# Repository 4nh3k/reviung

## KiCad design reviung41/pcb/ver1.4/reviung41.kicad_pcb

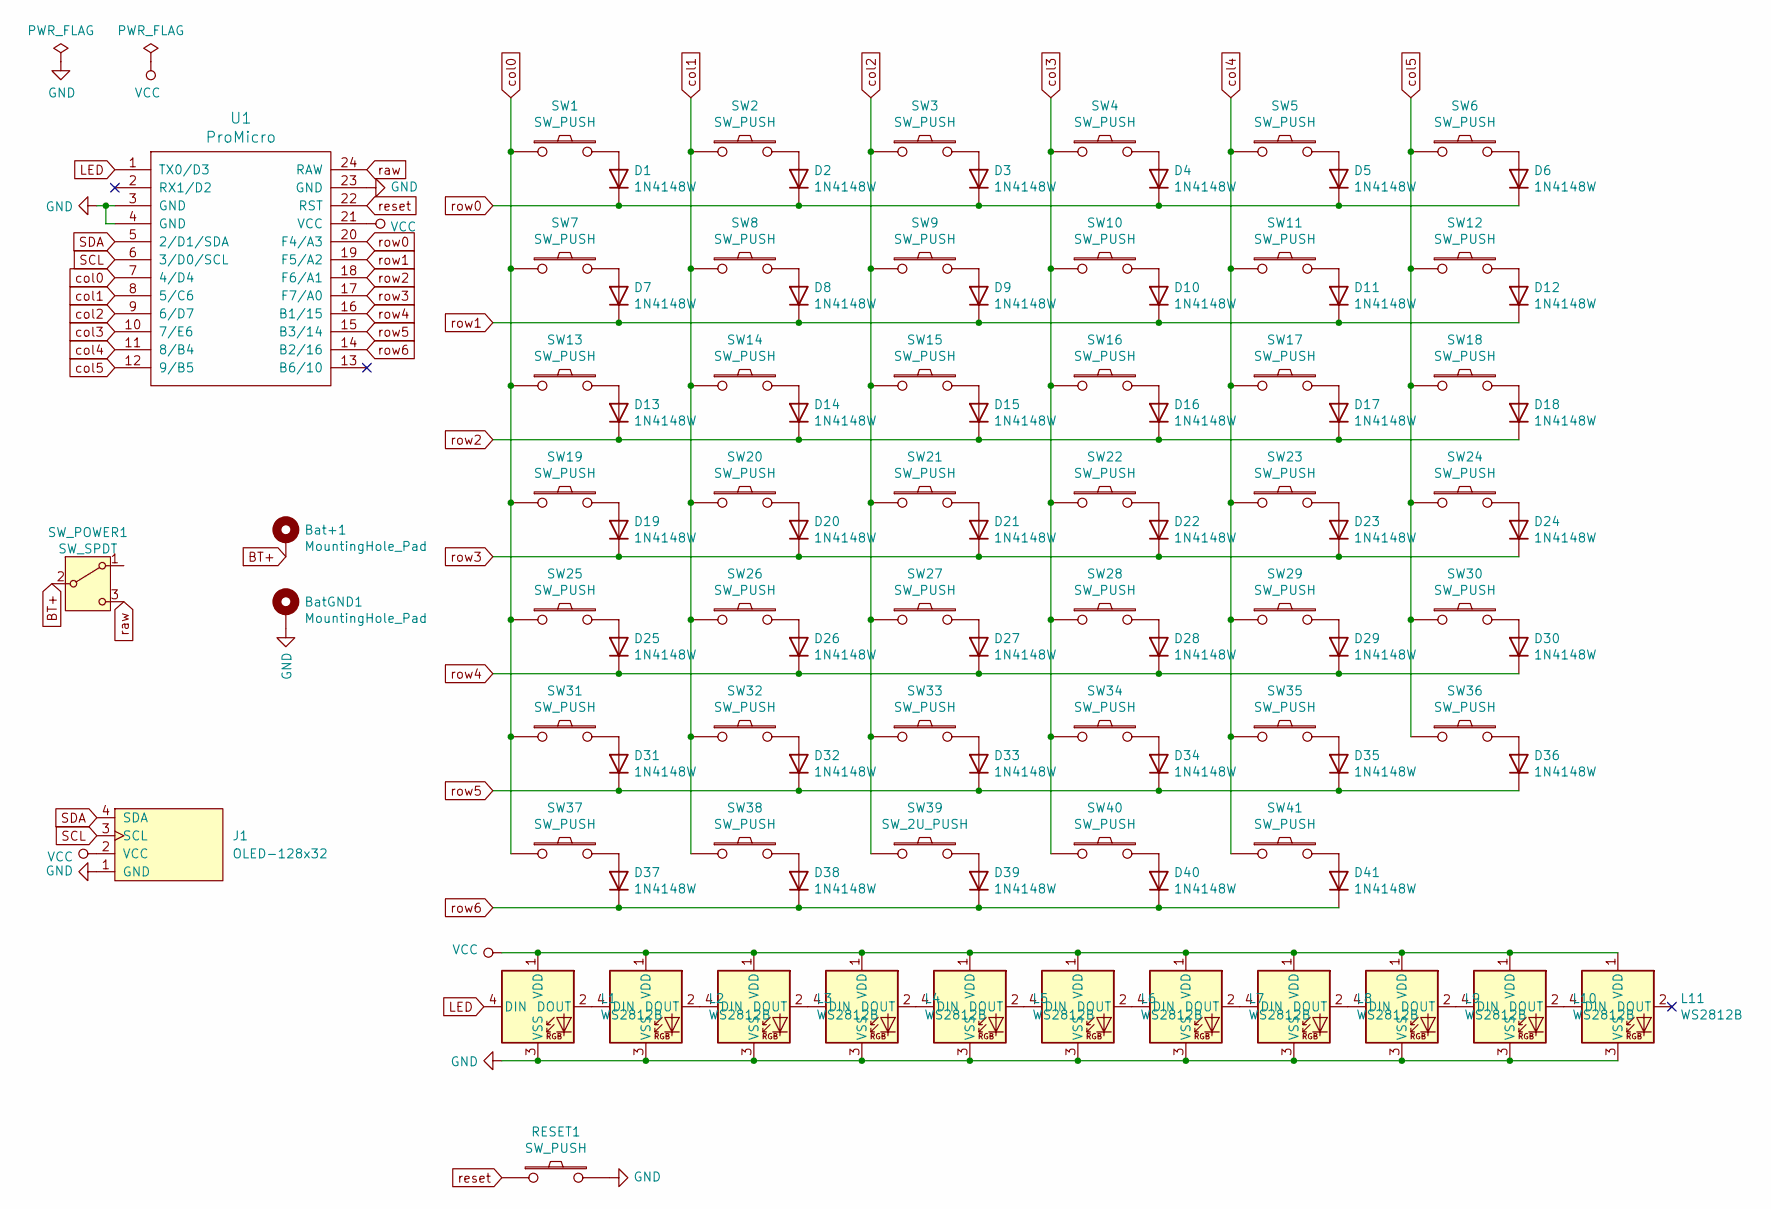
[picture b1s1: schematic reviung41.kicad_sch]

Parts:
Bat+1: MountingHole_Pad; batteryhole
BatGND1: MountingHole_Pad; batteryhole
D1, D2, D3, D4, D5, D6, D7, D8, D9, D10, D11, D12, D13, D14, D15, D16, D17, D18, D19, D20, D21, D22, D23, D24, D25, D26, D27, D28, D29, D30, D31, D32, D33, D34, D35, D36, D37, D38, D39, D40, D41: 1N4148W; D3_SMD_1side
J1: OLED-128x32; SSD1306-0.91-OLED-4pin-128x32
L1, L2, L3, L4, L5, L6, L7, L8, L9, L10, L11: WS2812B; LED_WS2812B_PLCC4_5.0x5.0mm_P3.2mm
RESET1: SW_PUSH; ResetSW_1side
SW1, SW2, SW3, SW4, SW5, SW6, SW7, SW8, SW9, SW10, SW11, SW12, SW13, SW14, SW15, SW16, SW17, SW18, SW19, SW20, SW21, SW22, SW23, SW24, SW25, SW26, SW27, SW28, SW29, SW30, SW31, SW32, SW33, SW34, SW35, SW36, SW37, SW38, SW40, SW41: SW_PUSH; MXOnly-1U-Hotswap
SW39: SW_2U_PUSH; MXOnly-2U-Hotswap-ReversedStabilizers
SW_POWER1: SW_SPDT; SW_SPDT_PCM12
U1: ProMicro

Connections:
BT+: Bat+1.1, SW_POWER1.2 (B)
GND: BatGND1.1, J1.1 (GND), L1.3 (VSS), L2.3 (VSS), L3.3 (VSS), L4.3 (VSS), L5.3 (VSS), L6.3 (VSS), L7.3 (VSS), L8.3 (VSS), L9.3 (VSS), L10.3 (VSS), L11.3 (VSS), RESET1.2, U1.3 (GND), U1.4 (GND), U1.23 (GND)
LED: L1.4 (DIN), U1.1 (TX0/D3)
unnamed: D1.2 (A), SW1.2
unnamed: D2.2 (A), SW2.2
unnamed: D3.2 (A), SW3.2
unnamed: D4.2 (A), SW4.2
unnamed: D5.2 (A), SW5.2
unnamed: D6.2 (A), SW6.2
unnamed: D7.2 (A), SW7.2
unnamed: D8.2 (A), SW8.2
unnamed: D9.2 (A), SW9.2
unnamed: D10.2 (A), SW10.2
unnamed: D11.2 (A), SW11.2
unnamed: D12.2 (A), SW12.2
unnamed: D13.2 (A), SW13.2
unnamed: D14.2 (A), SW14.2
unnamed: D15.2 (A), SW15.2
unnamed: D16.2 (A), SW16.2
unnamed: D17.2 (A), SW17.2
unnamed: D18.2 (A), SW18.2
unnamed: D19.2 (A), SW19.2
unnamed: D20.2 (A), SW20.2
unnamed: D21.2 (A), SW21.2
unnamed: D22.2 (A), SW22.2
unnamed: D23.2 (A), SW23.2
unnamed: D24.2 (A), SW24.2
unnamed: D25.2 (A), SW25.2
unnamed: D26.2 (A), SW26.2
unnamed: D27.2 (A), SW27.2
unnamed: D28.2 (A), SW28.2
unnamed: D29.2 (A), SW29.2
unnamed: D30.2 (A), SW30.2
unnamed: D31.2 (A), SW31.2
unnamed: D32.2 (A), SW32.2
unnamed: D33.2 (A), SW33.2
unnamed: D34.2 (A), SW34.2
unnamed: D35.2 (A), SW35.2
unnamed: D36.2 (A), SW36.2
unnamed: D37.2 (A), SW37.2
unnamed: D38.2 (A), SW38.2
unnamed: D39.2 (A), SW39.2
unnamed: D40.2 (A), SW40.2
unnamed: D41.2 (A), SW41.2
unnamed: L1.2 (DOUT), L2.4 (DIN)
unnamed: L2.2 (DOUT), L3.4 (DIN)
unnamed: L3.2 (DOUT), L4.4 (DIN)
unnamed: L4.2 (DOUT), L5.4 (DIN)
unnamed: L5.2 (DOUT), L6.4 (DIN)
unnamed: L6.2 (DOUT), L7.4 (DIN)
unnamed: L7.2 (DOUT), L8.4 (DIN)
unnamed: L8.2 (DOUT), L9.4 (DIN)
unnamed: L9.2 (DOUT), L10.4 (DIN)
unnamed: L10.2 (DOUT), L11.4 (DIN)
SCL: J1.3 (SCL), U1.6 (3/D0/SCL)
SDA: J1.4 (SDA), U1.5 (2/D1/SDA)
VCC: J1.2 (VCC), L1.1 (VDD), L2.1 (VDD), L3.1 (VDD), L4.1 (VDD), L5.1 (VDD), L6.1 (VDD), L7.1 (VDD), L8.1 (VDD), L9.1 (VDD), L10.1 (VDD), L11.1 (VDD), U1.21 (VCC)
col0: SW1.1, SW7.1, SW13.1, SW19.1, SW25.1, SW31.1, SW37.1, U1.7 (4/D4)
col1: SW2.1, SW8.1, SW14.1, SW20.1, SW26.1, SW32.1, SW38.1, U1.8 (5/C6)
col2: SW3.1, SW9.1, SW15.1, SW21.1, SW27.1, SW33.1, SW39.1, U1.9 (6/D7)
col3: SW4.1, SW10.1, SW16.1, SW22.1, SW28.1, SW34.1, SW40.1, U1.10 (7/E6)
col4: SW5.1, SW11.1, SW17.1, SW23.1, SW29.1, SW35.1, SW41.1, U1.11 (8/B4)
col5: SW6.1, SW12.1, SW18.1, SW24.1, SW30.1, SW36.1, U1.12 (9/B5)
raw: SW_POWER1.3 (C), U1.24 (RAW)
reset: RESET1.1, U1.22 (RST)
row0: D1.1 (K), D2.1 (K), D3.1 (K), D4.1 (K), D5.1 (K), D6.1 (K), U1.20 (F4/A3)
row1: D7.1 (K), D8.1 (K), D9.1 (K), D10.1 (K), D11.1 (K), D12.1 (K), U1.19 (F5/A2)
row2: D13.1 (K), D14.1 (K), D15.1 (K), D16.1 (K), D17.1 (K), D18.1 (K), U1.18 (F6/A1)
row3: D19.1 (K), D20.1 (K), D21.1 (K), D22.1 (K), D23.1 (K), D24.1 (K), U1.17 (F7/A0)
row4: D25.1 (K), D26.1 (K), D27.1 (K), D28.1 (K), D29.1 (K), D30.1 (K), U1.16 (B1/15)
row5: D31.1 (K), D32.1 (K), D33.1 (K), D34.1 (K), D35.1 (K), D36.1 (K), U1.15 (B3/14)
row6: D37.1 (K), D38.1 (K), D39.1 (K), D40.1 (K), D41.1 (K), U1.14 (B2/16)

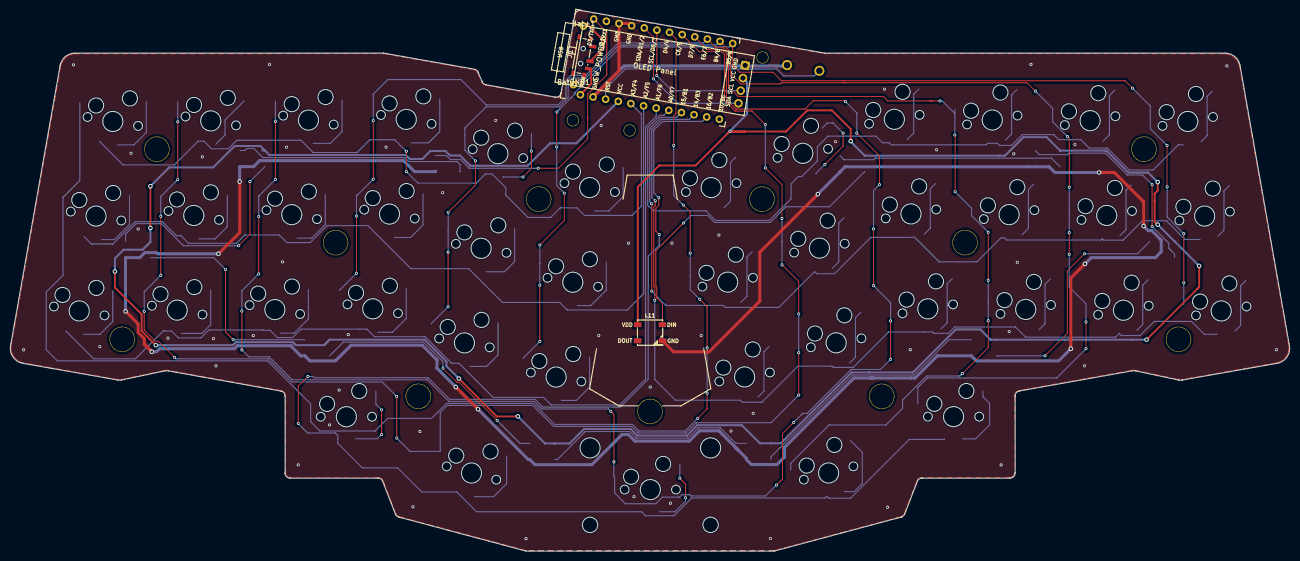
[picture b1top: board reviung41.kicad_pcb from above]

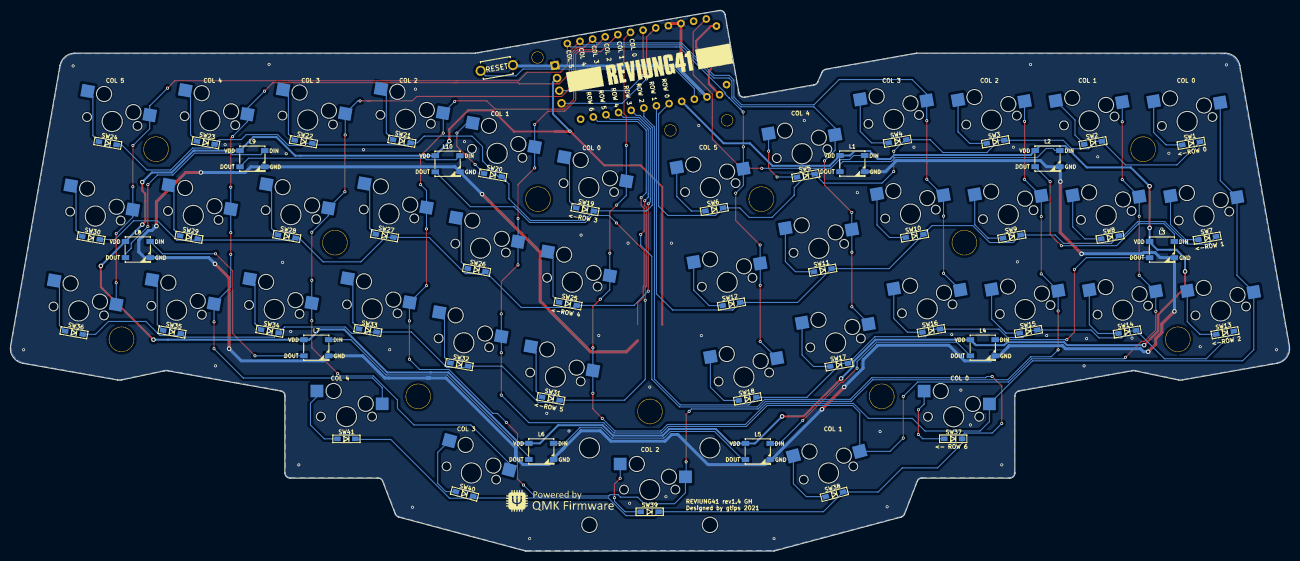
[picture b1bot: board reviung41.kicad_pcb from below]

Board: 2 copper layers, 253.3 x 107.1 mm, 113 parts (52 on the bottom side), 72 nets.

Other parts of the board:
H1: H1; HOLE
H2: H2; HOLE
H3: H3; HOLE
H4: H4; HOLE
H5: H5; HOLE
H6: H6; HOLE
H7: H7; HOLE
H8: H8; HOLE
H9: H9; HOLE
H10: H10; HOLE
H11: H11; HOLE
H12: H12; HOLE_2.2mm
H13: H13; HOLE_2.2mm
H14: H14; HOLE_2.2mm

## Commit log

2024-04-14 add oled and switch, hole for battery
